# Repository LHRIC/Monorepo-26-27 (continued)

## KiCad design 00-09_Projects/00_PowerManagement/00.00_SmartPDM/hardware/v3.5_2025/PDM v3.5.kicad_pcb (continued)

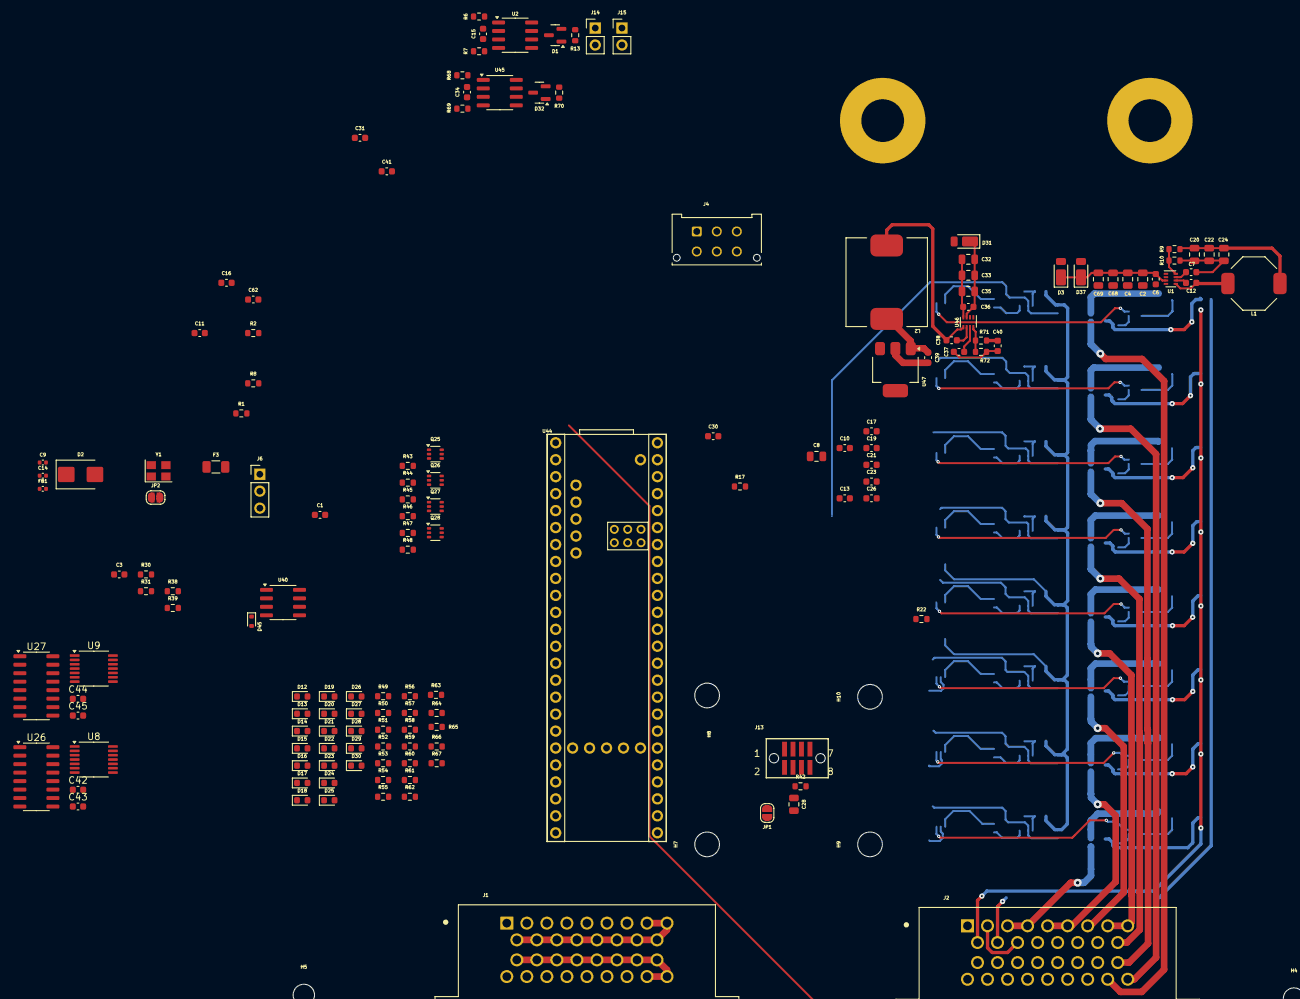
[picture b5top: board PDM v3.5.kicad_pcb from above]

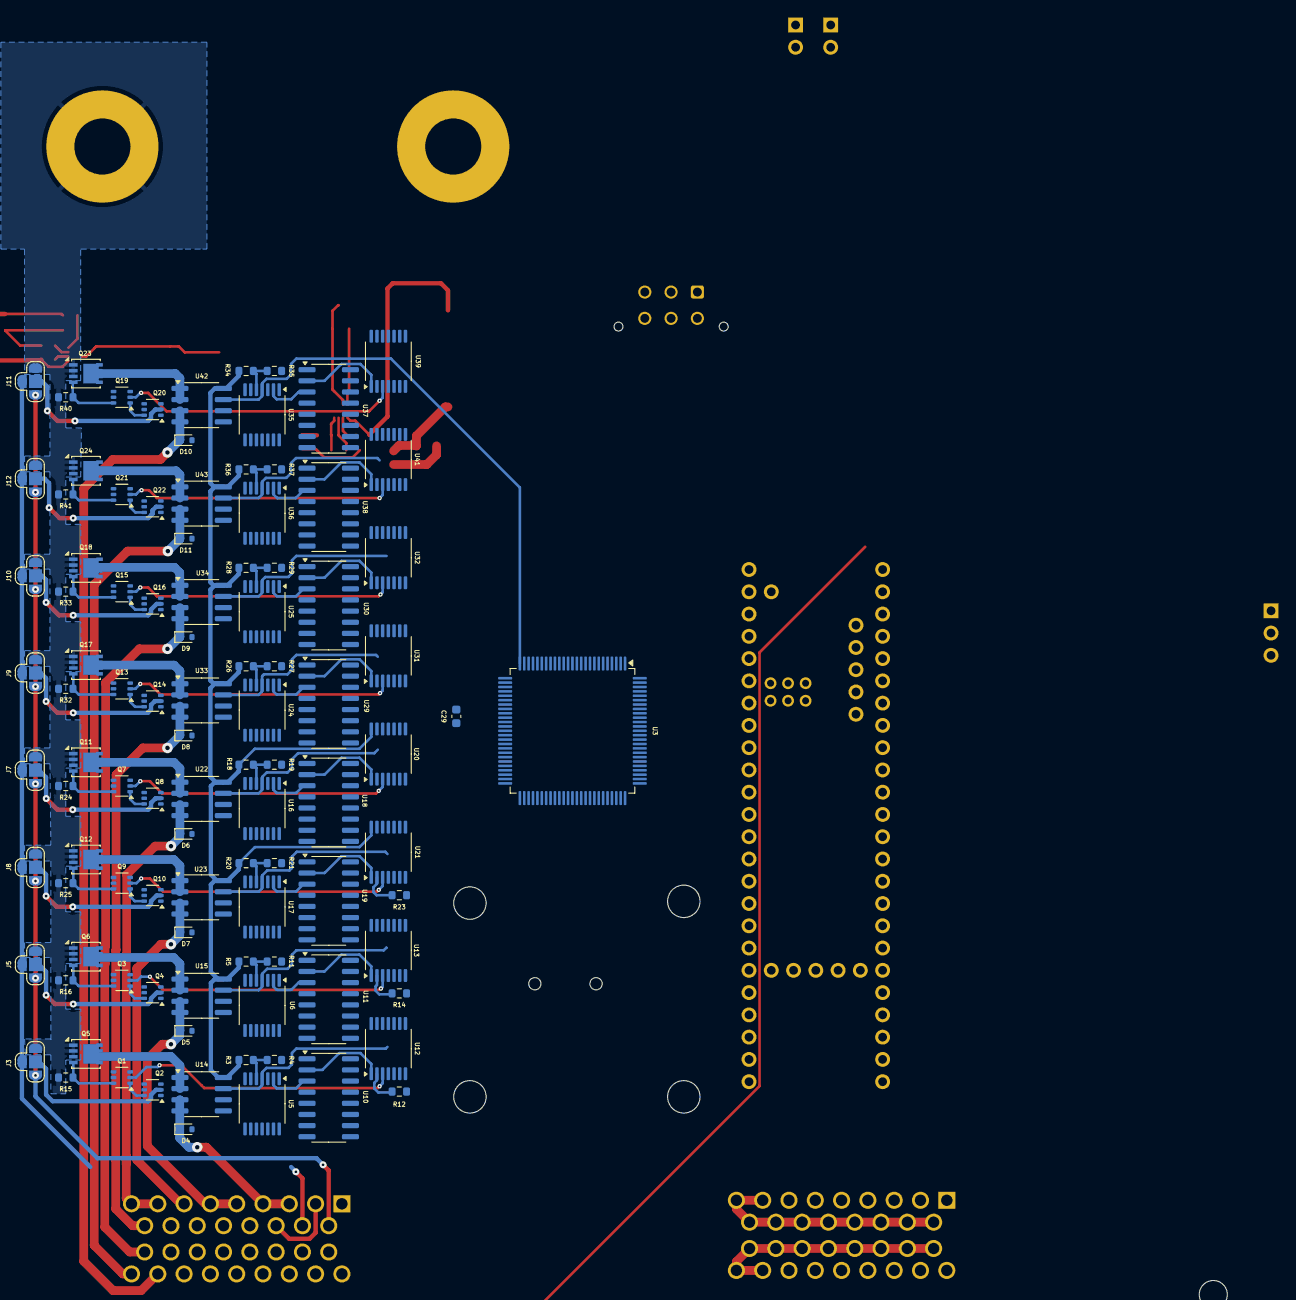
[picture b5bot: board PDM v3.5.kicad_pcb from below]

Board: 2 copper layers, 254 parts (101 on the bottom side), 180 nets.
